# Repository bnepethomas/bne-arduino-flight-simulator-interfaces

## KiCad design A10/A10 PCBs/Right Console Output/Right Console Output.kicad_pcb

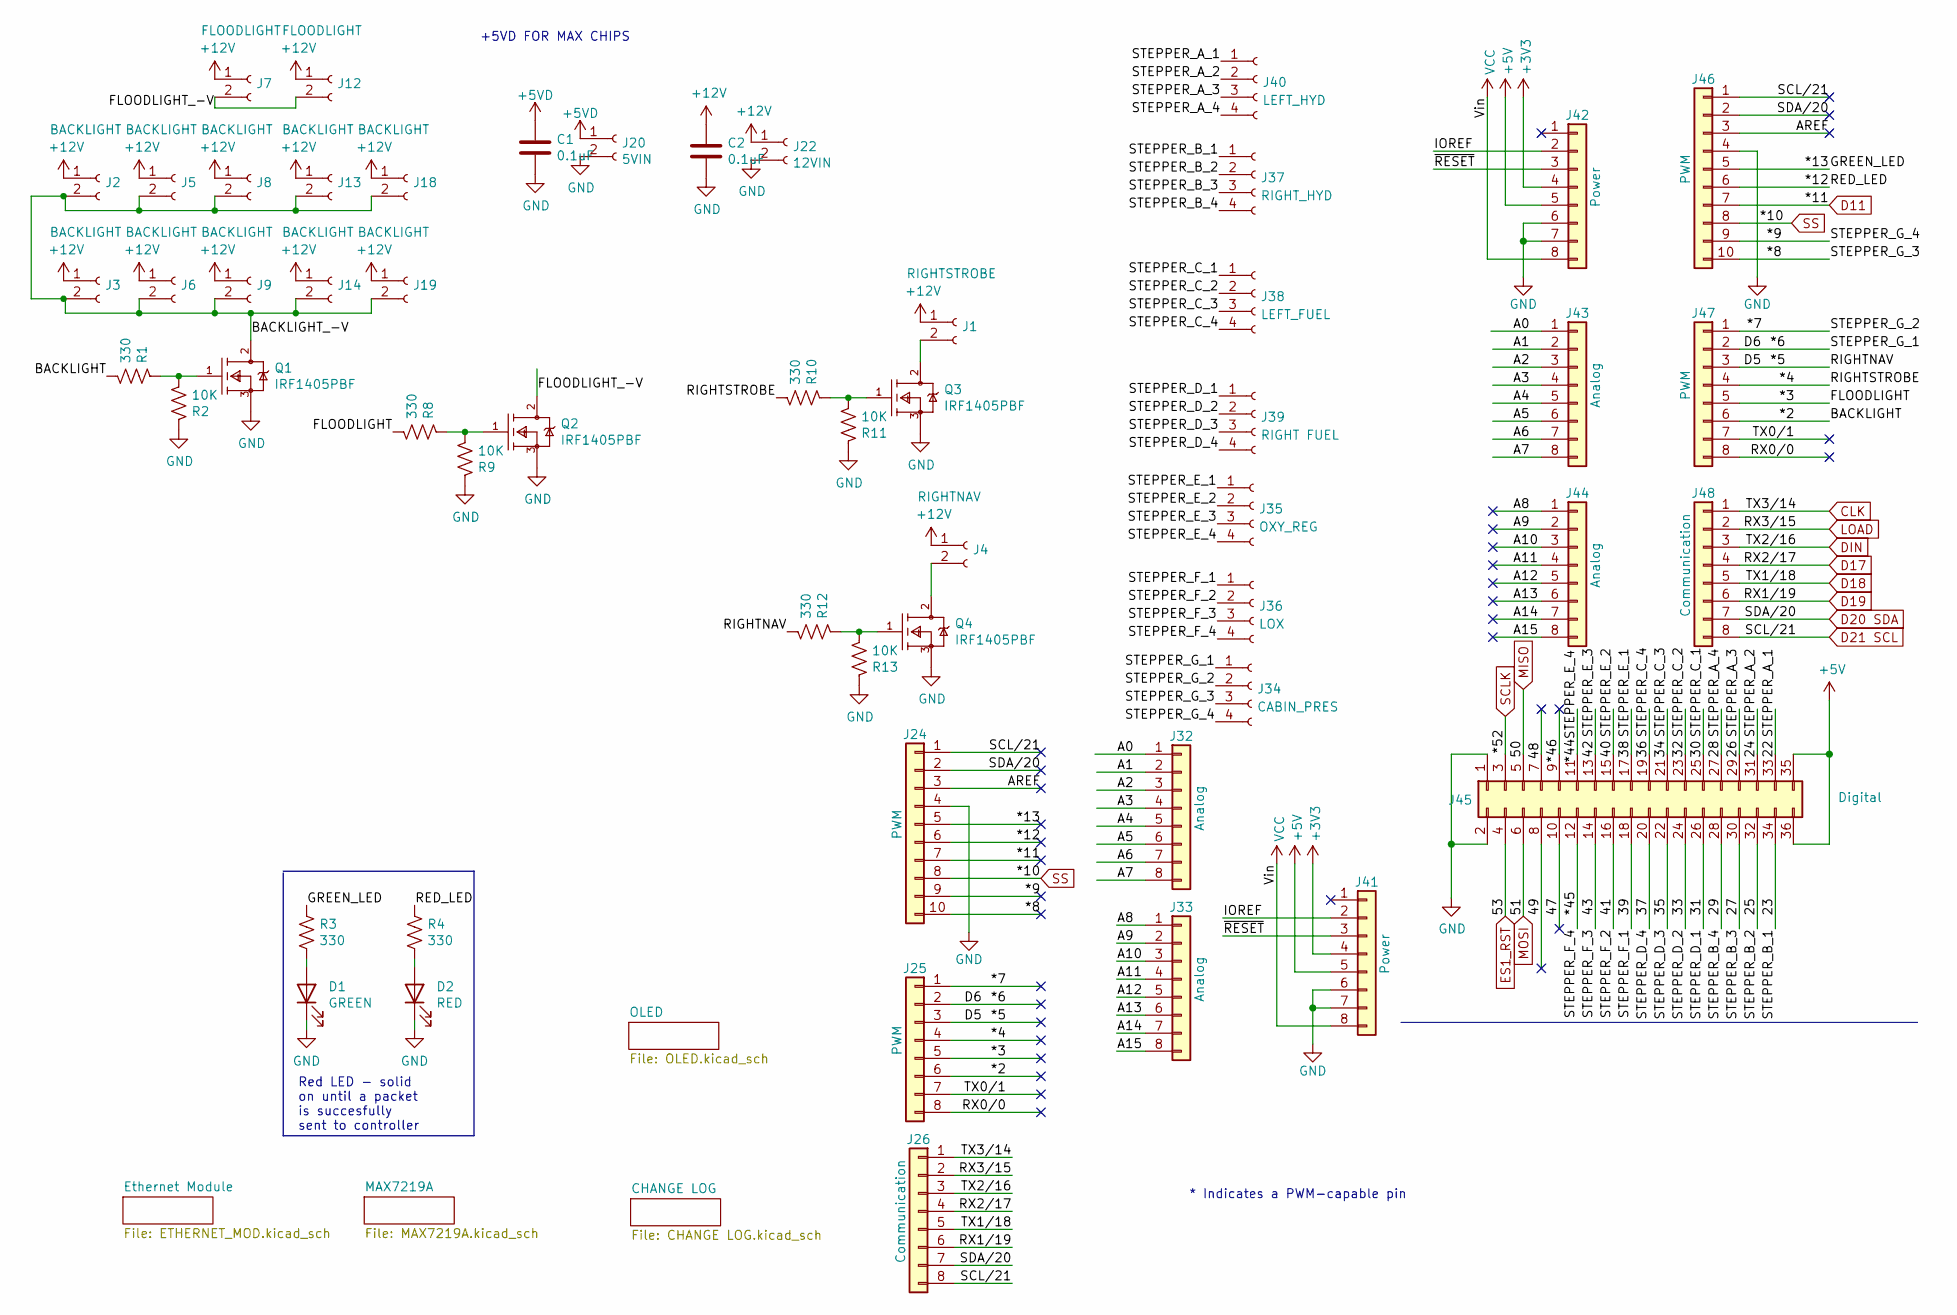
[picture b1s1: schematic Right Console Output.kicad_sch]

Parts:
C1, C2: 0.1uF; C_Disc_D4.3mm_W1.9mm_P5.00mm
D1: GREEN; LED_D3.0mm
D2: RED; LED_D3.0mm
J1: RIGHTSTROBE; Molex_KK-254_AE-6410-02A_1x02_P2.54mm_Vertical
J2, J3, J5, J6, J8, J9, J13, J14, J18, J19: BACKLIGHT; Molex_KK-254_AE-6410-02A_1x02_P2.54mm_Vertical
J4: RIGHTNAV; Molex_KK-254_AE-6410-02A_1x02_P2.54mm_Vertical
J7, J12: FLOODLIGHT; Molex_KK-254_AE-6410-02A_1x02_P2.54mm_Vertical
J20: 5VIN; BarrelJack_Horizontal
J22: 12VIN; BarrelJack_Horizontal
J24, J46: PWM; PinSocket_1x10_P2.54mm_Vertical
J25, J47: PWM; PinSocket_1x08_P2.54mm_Vertical
J26, J48: Communication; PinSocket_1x08_P2.54mm_Vertical
J32, J33, J43, J44: Analog; PinSocket_1x08_P2.54mm_Vertical
J34: CABIN_PRES; Molex_KK-254_AE-6410-04A_1x04_P2.54mm_Vertical
J35: OXY_REG; Molex_KK-254_AE-6410-04A_1x04_P2.54mm_Vertical
J36: LOX; Molex_KK-254_AE-6410-04A_1x04_P2.54mm_Vertical
J37: RIGHT_HYD; Molex_KK-254_AE-6410-04A_1x04_P2.54mm_Vertical
J38: LEFT_FUEL; Molex_KK-254_AE-6410-04A_1x04_P2.54mm_Vertical
J39: RIGHT FUEL; Molex_KK-254_AE-6410-04A_1x04_P2.54mm_Vertical
J40: LEFT_HYD; Molex_KK-254_AE-6410-04A_1x04_P2.54mm_Vertical
J41, J42: Power; PinSocket_1x08_P2.54mm_Vertical
J45: Digital; PinSocket_2x18_P2.54mm_Vertical
Q1, Q2, Q3, Q4: IRF1405PBF; TO-220-3_Vertical; mouser part number 942-IRF1405PBF; digikey description MOSFET N-CH 55V 169A TO-220AB
R1, R3, R4, R8, R10, R12: 330; R_Axial_DIN0204_L3.6mm_D1.6mm_P2.54mm_Vertical
R2, R9, R11, R13: 10K; R_Axial_DIN0204_L3.6mm_D1.6mm_P2.54mm_Vertical

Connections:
+3V3: J41.4, J42.4; also elsewhere on the board
+5V: J41.5, J42.5, J45.35, J45.36
+5VD: C1.1, J20.1; also elsewhere on the board
+12V: C2.1, J1.1, J2.1, J3.1, J4.1, J5.1, J6.1, J7.1, J8.1, J9.1, J12.1, J13.1, J14.1, J18.1, J19.1, J22.1
/22: J40.1, J45.33
/23: J37.1, J45.34
/24: J40.2, J45.31
/25: J37.2, J45.32
/26: J40.3, J45.29
/27: J37.3, J45.30
/28: J40.4, J45.27
/29: J37.4, J45.28
/30: J38.1, J45.25
/31: J39.1, J45.26
/32: J38.2, J45.23
/33: J39.2, J45.24
/34: J38.3, J45.21
/35: J39.3, J45.22
/36: J38.4, J45.19
/37: J39.4, J45.20
/38: J35.1, J45.17
/39: J36.1, J45.18
/40: J35.2, J45.15
/41: J36.2, J45.16
/42: J35.3, J45.13
/43: J36.3, J45.14
/47: J45.10
/48: J45.7
/49: J45.8
/*2: J25.6, J47.6, R1.2
/*3: J25.5, J47.5, R8.2
/*4: J25.4, J47.4, R10.2
/*5: J25.3, J47.3, R12.2
/*6: J25.2, J34.1, J47.2
/*7: J25.1, J34.2, J47.1
/*8: J24.10, J34.3, J46.10
/*9: J24.9, J34.4, J46.9
/*12: J24.6, J46.6, R4.1
/*13: J24.5, J46.5, R3.1
/*44: J35.4, J45.11
/*45: J36.4, J45.12
/*46: J45.9
/A0: J32.1, J43.1
/A1: J32.2, J43.2
/A2: J32.3, J43.3
/A3: J32.4, J43.4
/A4: J32.5, J43.5
/A5: J32.6, J43.6
/A6: J32.7, J43.7
/A7: J32.8, J43.8
/A8: J33.1, J44.1
/A9: J33.2, J44.2
/A10: J33.3, J44.3
/A11: J33.4, J44.4
/A12: J33.5, J44.5
/A13: J33.6, J44.6
/A14: J33.7, J44.7
/A15: J33.8, J44.8
/AREF: J24.3, J46.3
/BACKLIGHT_-V: J2.2, J3.2, J5.2, J6.2, J8.2, J9.2, J13.2, J14.2, J18.2, J19.2, Q1.2 (D)
/FLOODLIGHT_-V: J7.2, J12.2, Q2.2 (D)
/IOREF: J41.2, J42.2
/RX0/0: J25.8, J47.8
/TX0/1: J25.7, J47.7
/~RESET: J41.3, J42.3
CLK: J26.1, J48.1; also elsewhere on the board
D11: J24.7, J46.7
D17: J26.4, J48.4; also elsewhere on the board
D18: J26.5, J48.5; also elsewhere on the board
D19: J26.6, J48.6; also elsewhere on the board
D20 SDA: J24.2, J26.7, J46.2, J48.7; also elsewhere on the board
D21 SCL: J24.1, J26.8, J46.1, J48.8; also elsewhere on the board
DIN: J26.3, J48.3; also elsewhere on the board
ES1_RST: J45.4; also elsewhere on the board
GND: C1.2, C2.2, D1.1 (K), D2.1 (K), J20.2, J22.2, J24.4, J41.6, J41.7, J42.6, J42.7, J45.1, J45.2, J46.4, Q1.3 (S), Q2.3 (S), Q3.3 (S), Q4.3 (S), R2.1, R9.1, R11.1, R13.1; also elsewhere on the board
LOAD: J26.2, J48.2; also elsewhere on the board
MISO: J45.5; also elsewhere on the board
MOSI: J45.6; also elsewhere on the board
unnamed: D1.2 (A), R3.2
unnamed: D2.2 (A), R4.2
unnamed: J1.2, Q3.2 (D)
unnamed: J4.2, Q4.2 (D)
unnamed: Q1.1 (G), R1.1, R2.2
unnamed: Q2.1 (G), R8.1, R9.2
unnamed: Q3.1 (G), R10.1, R11.2
unnamed: Q4.1 (G), R12.1, R13.2
SCLK: J45.3; also elsewhere on the board
SS: J24.8, J46.8; also elsewhere on the board
VCC: J41.8, J42.8

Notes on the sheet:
Red LED - solid on until a packet is succesfully sent to controller
+5VD FOR MAX CHIPS
* Indicates a PWM-capable pin

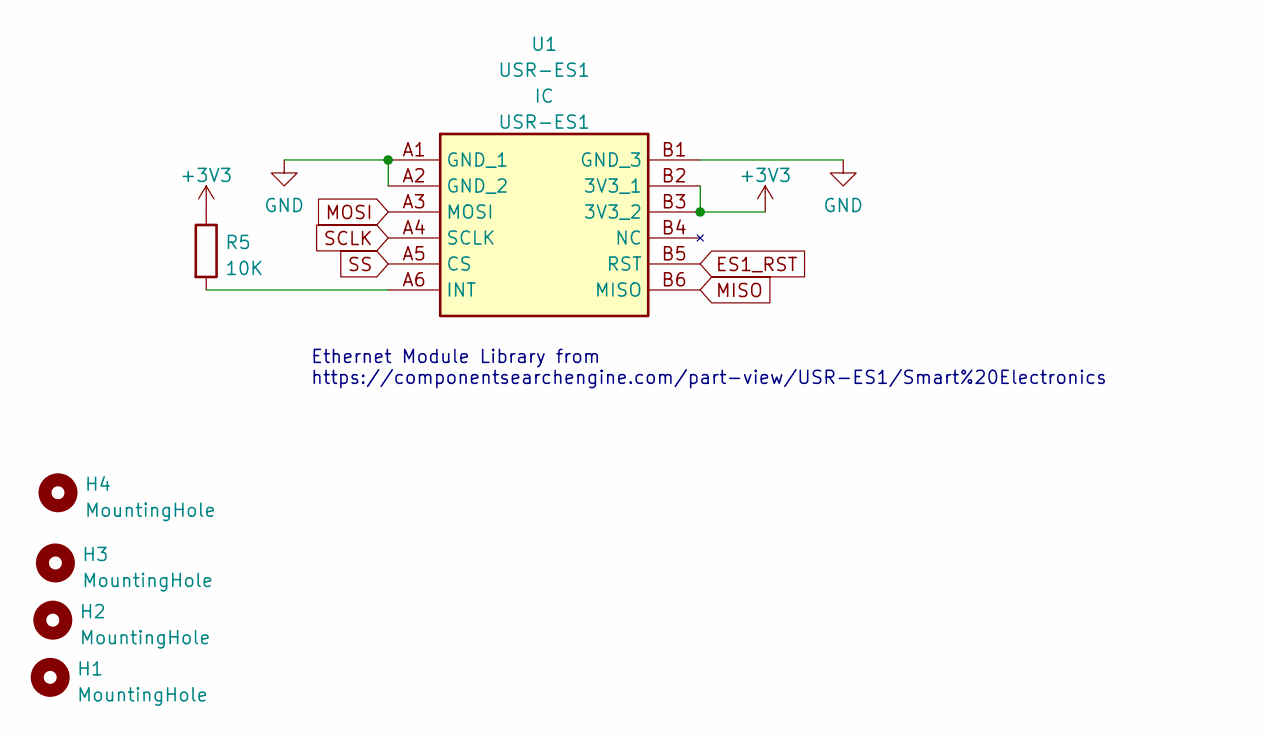
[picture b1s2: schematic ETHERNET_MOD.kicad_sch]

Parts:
H1, H2, H3, H4: MountingHole; MountingHole_3.2mm
R5: 10K; R_Axial_DIN0204_L3.6mm_D1.6mm_P2.54mm_Vertical
U1: USR-ES1; USRES1; Manufacturer_Part_Number USR-ES1

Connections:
+3V3: R5.1, U1.B2 (3V3_1), U1.B3 (3V3_2); also elsewhere on the board
ES1_RST: U1.B5 (RST); also elsewhere on the board
GND: U1.A1 (GND_1), U1.A2 (GND_2), U1.B1 (GND_3); also elsewhere on the board
MISO: U1.B6 (MISO); also elsewhere on the board
MOSI: U1.A3 (MOSI); also elsewhere on the board
unnamed: R5.2, U1.A6 (INT)
SCLK: U1.A4 (SCLK); also elsewhere on the board
SS: U1.A5 (CS); also elsewhere on the board

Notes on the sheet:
Ethernet Module Library from https://componentsearchengine.com/part-view/USR-ES1/Smart%20Electronics

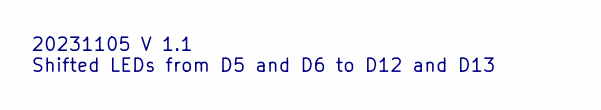
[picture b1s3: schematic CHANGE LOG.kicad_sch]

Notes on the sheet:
20231105 V 1.1 Shifted LEDs from D5 and D6 to D12 and D13

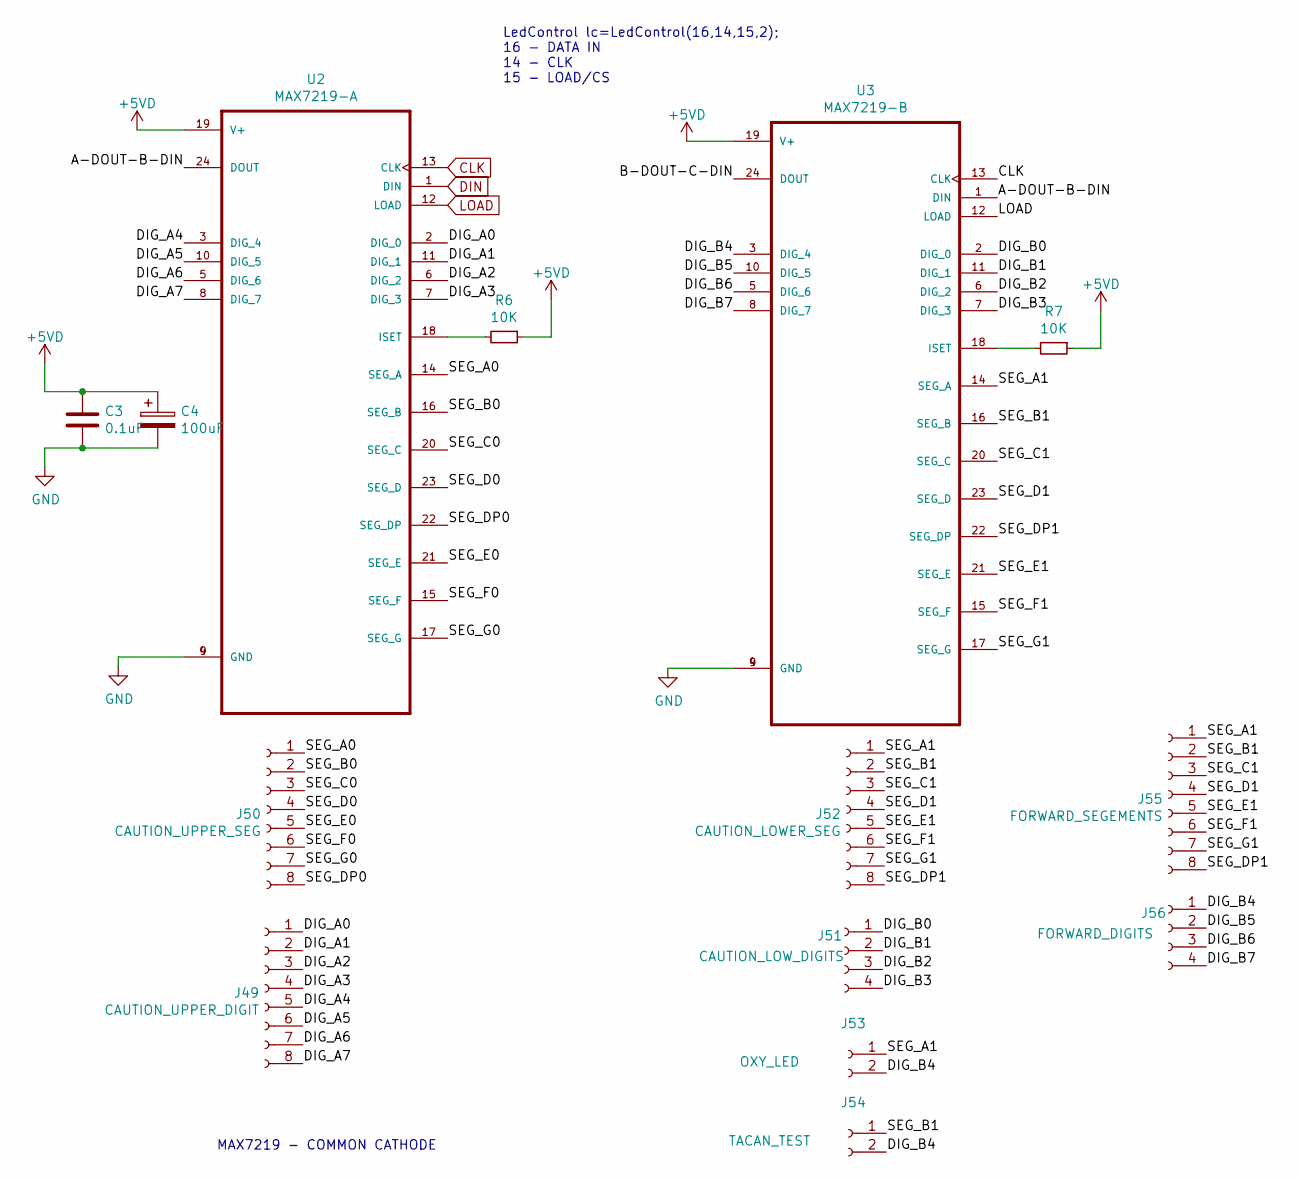
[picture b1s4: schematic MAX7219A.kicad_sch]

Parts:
C3: 0.1uF; C_Disc_D5.1mm_W3.2mm_P5.00mm
C4: 100uF; CP_Radial_D8.0mm_P5.00mm
J49: CAUTION_UPPER_DIGIT; Molex_KK-254_AE-6410-08A_1x08_P2.54mm_Vertical
J50: CAUTION_UPPER_SEG; Molex_KK-254_AE-6410-08A_1x08_P2.54mm_Vertical
J51: CAUTION_LOW_DIGITS; Molex_KK-254_AE-6410-04A_1x04_P2.54mm_Vertical
J52: CAUTION_LOWER_SEG; Molex_KK-254_AE-6410-08A_1x08_P2.54mm_Vertical
J53: OXY_LED; Molex_KK-254_AE-6410-02A_1x02_P2.54mm_Vertical
J54: TACAN_TEST; Molex_KK-254_AE-6410-02A_1x02_P2.54mm_Vertical
J55: FORWARD_SEGEMENTS; Molex_KK-254_AE-6410-08A_1x08_P2.54mm_Vertical
J56: FORWARD_DIGITS; Molex_KK-254_AE-6410-04A_1x04_P2.54mm_Vertical
R6, R7: 10K; R_Axial_DIN0204_L3.6mm_D1.6mm_P2.54mm_Vertical
U2: MAX7219-A; DIP-24_W7.62mm_Socket
U3: MAX7219-B; DIP-24_W7.62mm_Socket

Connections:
+5VD: C3.1, C4.1, R6.1, R7.1, U2.19 (V+), U3.19 (V+); also elsewhere on the board
/MAX7219A/A-DOUT-B-DIN: U2.24 (DOUT), U3.1 (DIN)
/MAX7219A/B-DOUT-C-DIN: U3.24 (DOUT)
/MAX7219A/DIG_A0: J49.1, U2.2 (DIG_0)
/MAX7219A/DIG_A1: J49.2, U2.11 (DIG_1)
/MAX7219A/DIG_A2: J49.3, U2.6 (DIG_2)
/MAX7219A/DIG_A3: J49.4, U2.7 (DIG_3)
/MAX7219A/DIG_A4: J49.5, U2.3 (DIG_4)
/MAX7219A/DIG_A5: J49.6, U2.10 (DIG_5)
/MAX7219A/DIG_A6: J49.7, U2.5 (DIG_6)
/MAX7219A/DIG_A7: J49.8, U2.8 (DIG_7)
/MAX7219A/DIG_B0: J51.1, U3.2 (DIG_0)
/MAX7219A/DIG_B1: J51.2, U3.11 (DIG_1)
/MAX7219A/DIG_B2: J51.3, U3.6 (DIG_2)
/MAX7219A/DIG_B3: J51.4, U3.7 (DIG_3)
/MAX7219A/DIG_B4: J53.2, J54.2, J56.1, U3.3 (DIG_4)
/MAX7219A/DIG_B5: J56.2, U3.10 (DIG_5)
/MAX7219A/DIG_B6: J56.3, U3.5 (DIG_6)
/MAX7219A/DIG_B7: J56.4, U3.8 (DIG_7)
/MAX7219A/SEG_A0: J50.1, U2.14 (SEG_A)
/MAX7219A/SEG_A1: J52.1, J53.1, J55.1, U3.14 (SEG_A)
/MAX7219A/SEG_B0: J50.2, U2.16 (SEG_B)
/MAX7219A/SEG_B1: J52.2, J54.1, J55.2, U3.16 (SEG_B)
/MAX7219A/SEG_C0: J50.3, U2.20 (SEG_C)
/MAX7219A/SEG_C1: J52.3, J55.3, U3.20 (SEG_C)
/MAX7219A/SEG_D0: J50.4, U2.23 (SEG_D)
/MAX7219A/SEG_D1: J52.4, J55.4, U3.23 (SEG_D)
/MAX7219A/SEG_DP0: J50.8, U2.22 (SEG_DP)
/MAX7219A/SEG_DP1: J52.8, J55.8, U3.22 (SEG_DP)
/MAX7219A/SEG_E0: J50.5, U2.21 (SEG_E)
/MAX7219A/SEG_E1: J52.5, J55.5, U3.21 (SEG_E)
/MAX7219A/SEG_F0: J50.6, U2.15 (SEG_F)
/MAX7219A/SEG_F1: J52.6, J55.6, U3.15 (SEG_F)
/MAX7219A/SEG_G0: J50.7, U2.17 (SEG_G)
/MAX7219A/SEG_G1: J52.7, J55.7, U3.17 (SEG_G)
CLK: U2.13 (CLK), U3.13 (CLK); also elsewhere on the board
DIN: U2.1 (DIN); also elsewhere on the board
GND: C3.2, C4.2, U2.4 (GND), U2.9 (GND), U3.4 (GND), U3.9 (GND); also elsewhere on the board
LOAD: U2.12 (LOAD), U3.12 (LOAD); also elsewhere on the board
unnamed: R6.2, U2.18 (ISET)
unnamed: R7.2, U3.18 (ISET)

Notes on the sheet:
LedControl lc=LedControl(16,14,15,2); 16 - DATA IN 14 - CLK 15 - LOAD/CS
MAX7219 - COMMON CATHODE

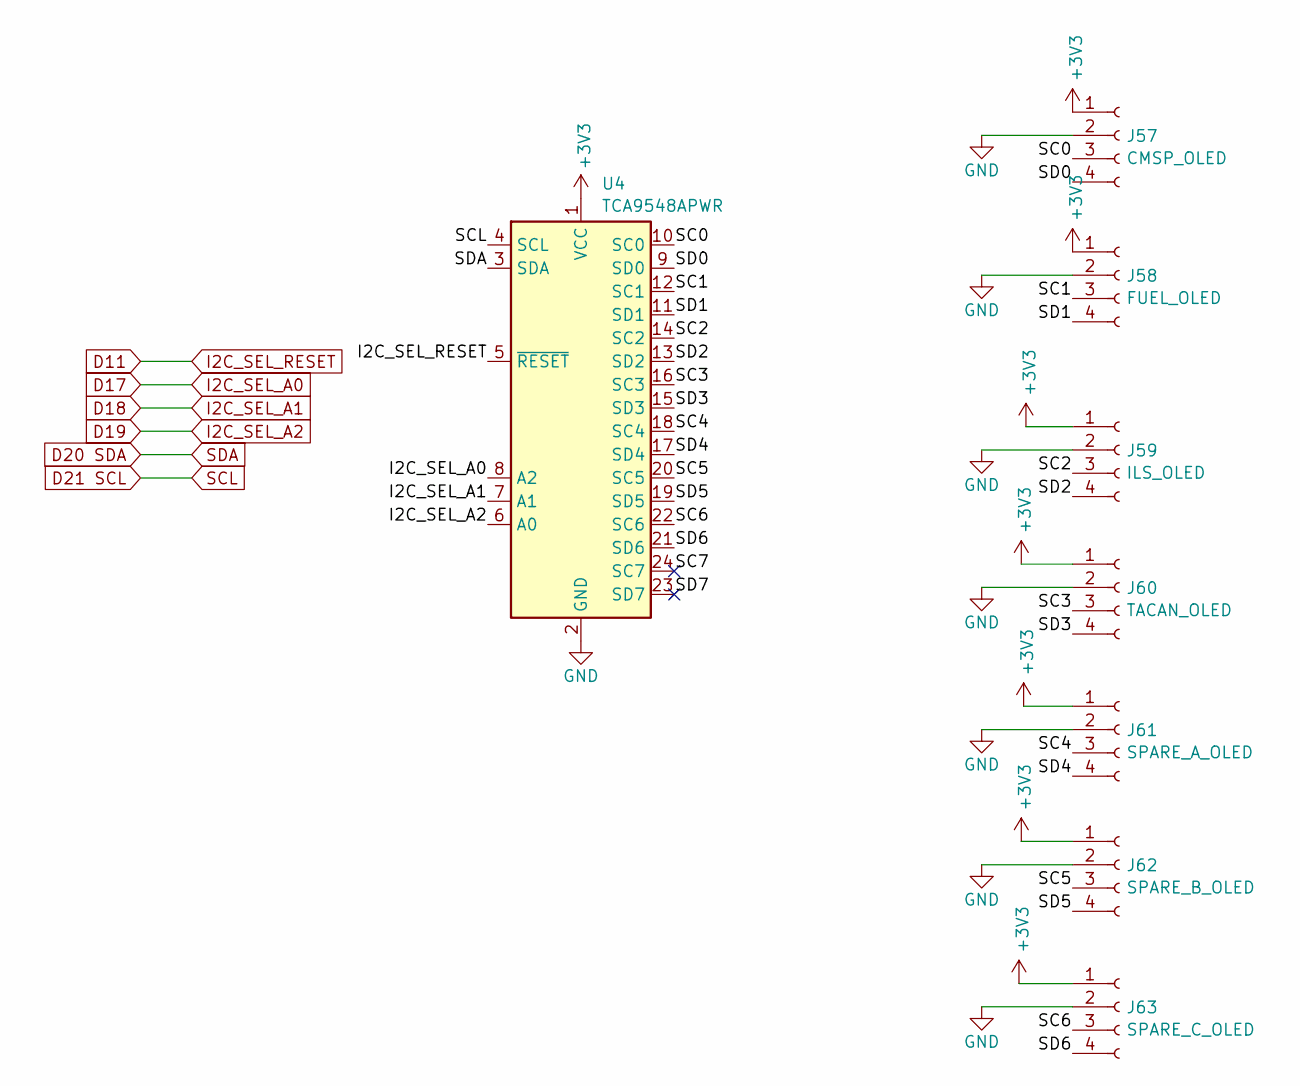
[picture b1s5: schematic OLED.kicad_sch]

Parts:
J57: CMSP_OLED; Molex_KK-254_AE-6410-04A_1x04_P2.54mm_Vertical
J58: FUEL_OLED; Molex_KK-254_AE-6410-04A_1x04_P2.54mm_Vertical
J59: ILS_OLED; Molex_KK-254_AE-6410-04A_1x04_P2.54mm_Vertical
J60: TACAN_OLED; Molex_KK-254_AE-6410-04A_1x04_P2.54mm_Vertical
J61: SPARE_A_OLED; Molex_KK-254_AE-6410-04A_1x04_P2.54mm_Vertical
J62: SPARE_B_OLED; Molex_KK-254_AE-6410-04A_1x04_P2.54mm_Vertical
J63: SPARE_C_OLED; Molex_KK-254_AE-6410-04A_1x04_P2.54mm_Vertical
U4: TCA9548APWR; DIP-24_TCA9548A

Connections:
+3V3: J57.1, J58.1, J59.1, J60.1, J61.1, J62.1, J63.1, U4.1 (VCC); also elsewhere on the board
/OLED/SC0: J57.3, U4.10 (SC0)
/OLED/SC1: J58.3, U4.12 (SC1)
/OLED/SC2: J59.3, U4.14 (SC2)
/OLED/SC3: J60.3, U4.16 (SC3)
/OLED/SC4: J61.3, U4.18 (SC4)
/OLED/SC5: J62.3, U4.20 (SC5)
/OLED/SC6: J63.3, U4.22 (SC6)
/OLED/SC7: U4.24 (SC7)
/OLED/SD0: J57.4, U4.9 (SD0)
/OLED/SD1: J58.4, U4.11 (SD1)
/OLED/SD2: J59.4, U4.13 (SD2)
/OLED/SD3: J60.4, U4.15 (SD3)
/OLED/SD4: J61.4, U4.17 (SD4)
/OLED/SD5: J62.4, U4.19 (SD5)
/OLED/SD6: J63.4, U4.21 (SD6)
/OLED/SD7: U4.23 (SD7)
D16: U4.5 (~RESET)
D17: U4.8 (A2); also elsewhere on the board
D18: U4.7 (A1); also elsewhere on the board
D19: U4.6 (A0); also elsewhere on the board
D20 SDA: U4.3 (SDA); also elsewhere on the board
D21 SCL: U4.4 (SCL); also elsewhere on the board
GND: J57.2, J58.2, J59.2, J60.2, J61.2, J62.2, J63.2, U4.2 (GND); also elsewhere on the board

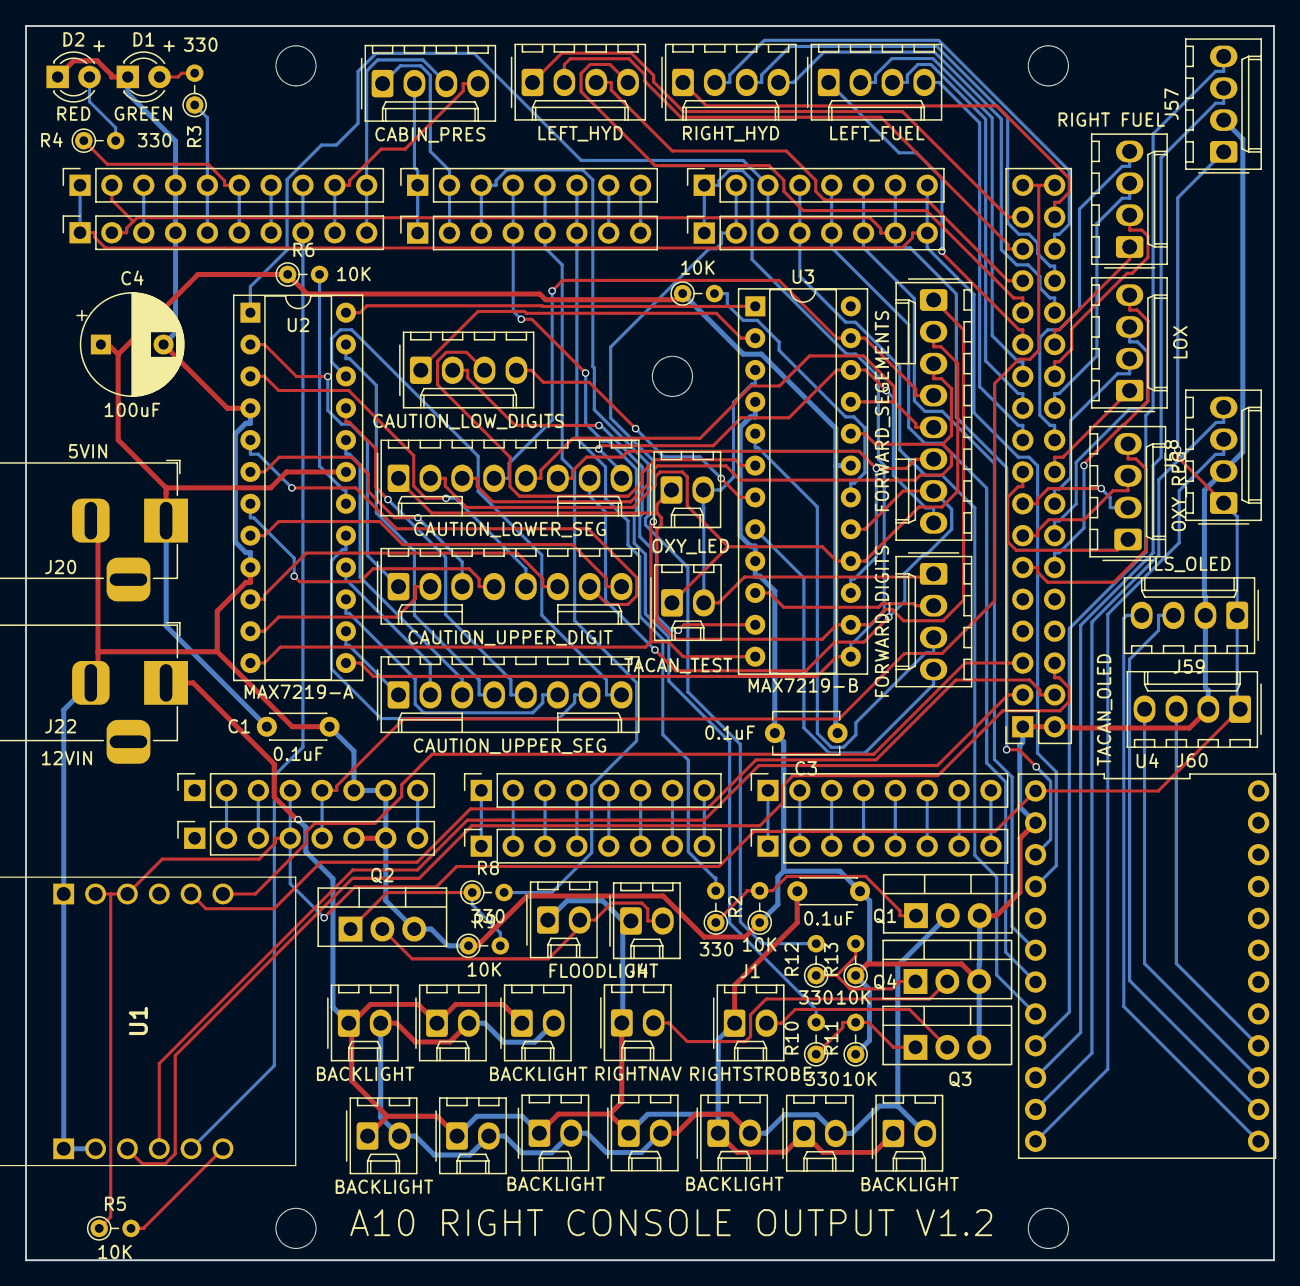
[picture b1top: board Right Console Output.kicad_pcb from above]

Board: 2 copper layers, 99.5 x 98.4 mm, 80 parts (0 on the bottom side), 129 nets.

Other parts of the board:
MH1: MountingHole_3.2mm

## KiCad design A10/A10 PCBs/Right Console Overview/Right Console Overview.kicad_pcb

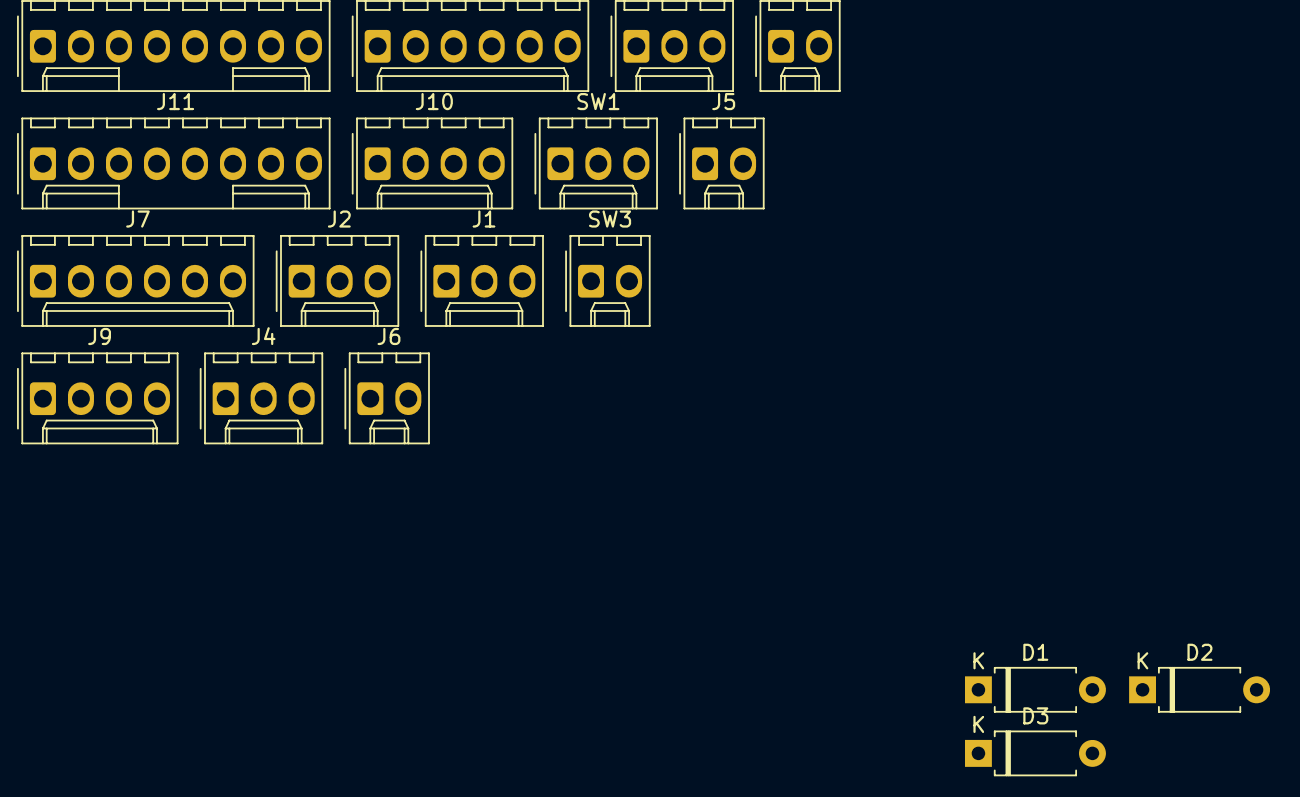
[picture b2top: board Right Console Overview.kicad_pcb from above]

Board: 2 copper layers, 18 parts (0 on the bottom side), 10 nets, no tracks yet.

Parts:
D1, D2, D3: D; D_A-405_P7.62mm_Horizontal
J1, J2, J3, J4: Conn_01x03_Female; Molex_KK-254_AE-6410-03A_1x03_P2.54mm_Vertical
J5, J6: Conn_01x02_Female; Molex_KK-254_AE-6410-02A_1x02_P2.54mm_Vertical
J7: TACAN ROTARY SWITCH; Molex_KK-254_AE-6410-06A_1x06_P2.54mm_Vertical
J8: Conn_01x08_Female; Molex_KK-254_AE-6410-08A_1x08_P2.54mm_Vertical
J9: I2C In; Molex_KK-254_AE-6410-04A_1x04_P2.54mm_Vertical
J10: I2C Out; Molex_KK-254_AE-6410-04A_1x04_P2.54mm_Vertical
J11: INPUT COLS; Molex_KK-254_AE-6410-08A_1x08_P2.54mm_Vertical
SW1: Right Encoder; Molex_KK-254_AE-6410-03A_1x03_P2.54mm_Vertical
SW2: SW_Rotary2x6; Molex_KK-254_AE-6410-06A_1x06_P2.54mm_Vertical
SW3: Test; Molex_KK-254_AE-6410-02A_1x02_P2.54mm_Vertical
SW4: Encoder_Push; Molex_KK-254_AE-6410-02A_1x02_P2.54mm_Vertical

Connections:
/TACAN/COL1: D3.2 (A), J11.1
/TACAN/COL2: D1.2 (A), J11.2
/TACAN/ROW1: J7.2, SW3.2, SW4.2
unnamed: D1.1 (K), SW3.1
unnamed: D2.1 (K), SW4.1
unnamed: D3.1 (K), J7.1
unnamed: J9.1, J10.1
unnamed: J9.2, J10.2
unnamed: J9.3, J10.3
unnamed: J9.4, J10.4

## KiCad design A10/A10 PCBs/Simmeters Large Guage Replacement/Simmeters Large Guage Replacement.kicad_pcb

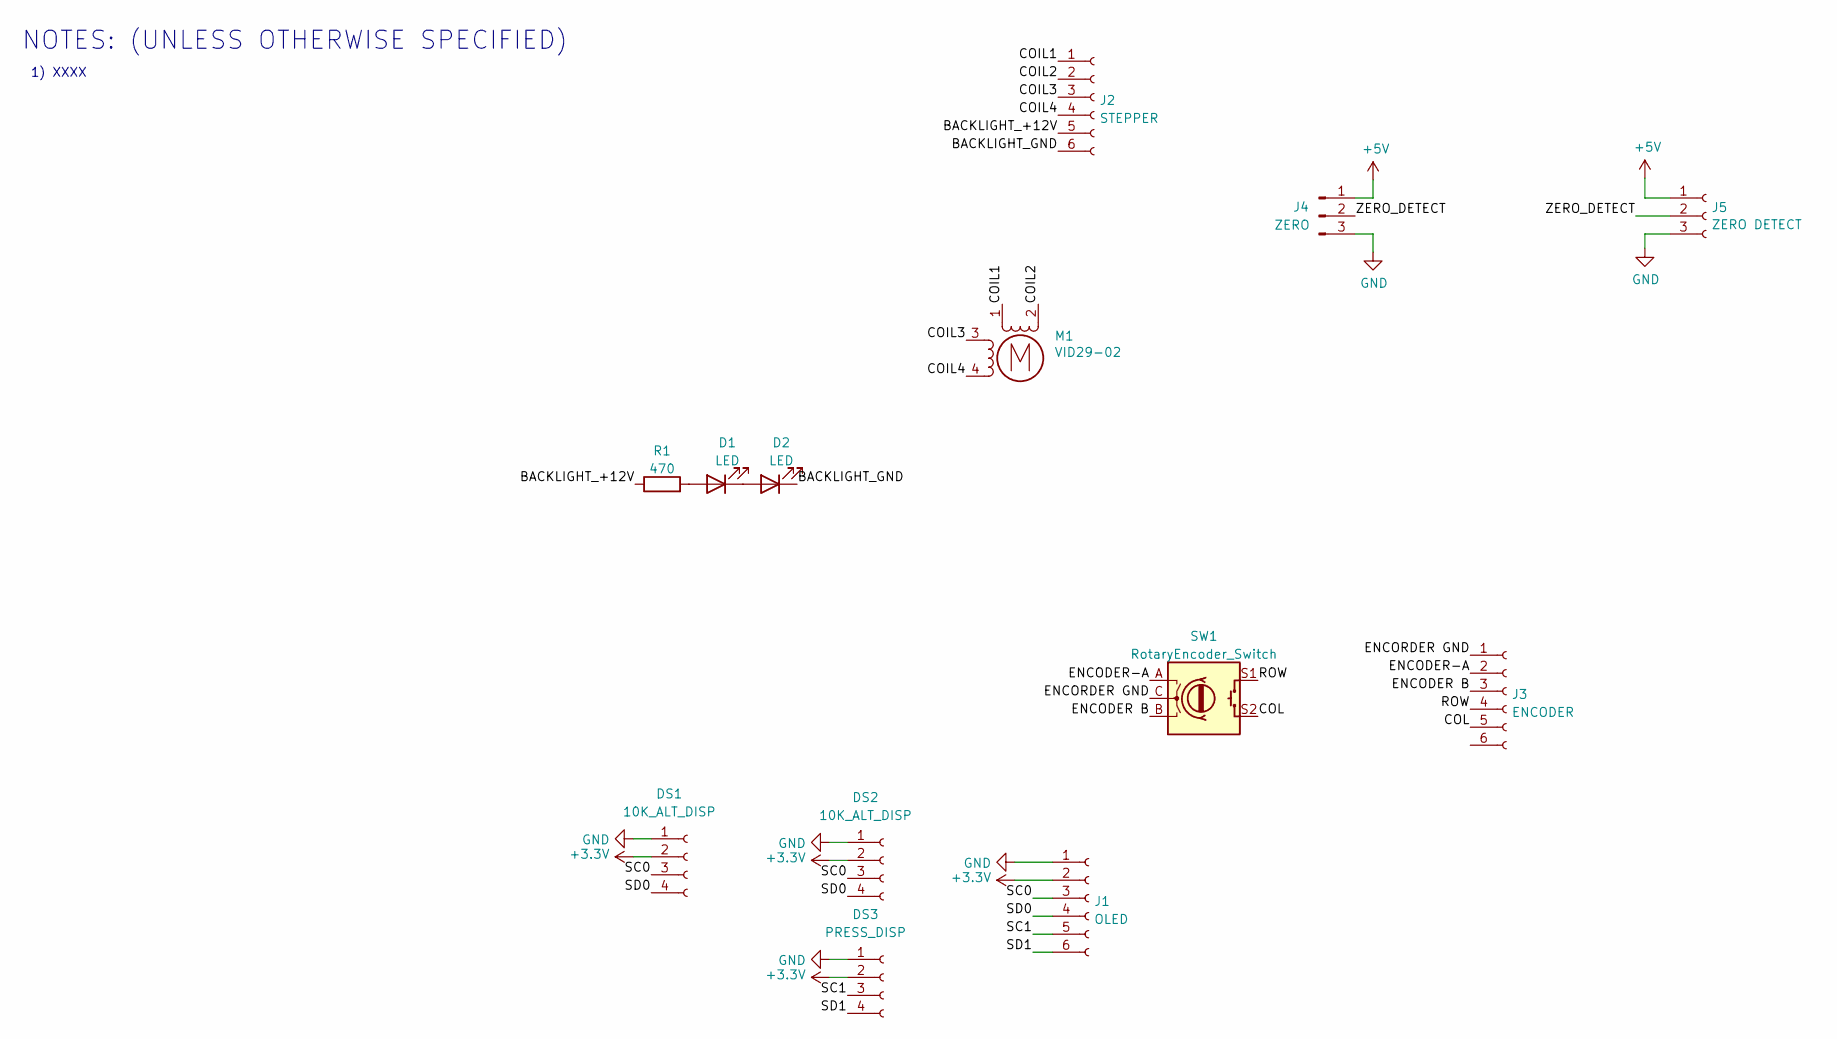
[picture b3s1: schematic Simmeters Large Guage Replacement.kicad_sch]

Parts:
D1, D2: LED; LED_D3.0mm
DS1, DS2: 10K_ALT_DISP; PinSocket_1x04_P2.54mm_Vertical
DS3: PRESS_DISP; PinSocket_1x04_P2.54mm_Vertical
J1: OLED; Molex_KK-254_AE-6410-06A_1x06_P2.54mm_Vertical
J2: STEPPER; Molex_KK-254_AE-6410-06A_1x06_P2.54mm_Vertical
J3: ENCODER; Molex_KK-254_AE-6410-06A_1x06_P2.54mm_Vertical
J4: ZERO; PinHeader_1x03_P2.54mm_Vertical
J5: ZERO DETECT; Molex_KK-254_AE-6410-03A_1x03_P2.54mm_Vertical
M1: VID29-02
R1: 470; R_Axial_DIN0204_L3.6mm_D1.6mm_P1.90mm_Vertical
SW1: RotaryEncoder_Switch; RotaryEncoder_Alps_EC11E-Switch_Vertical_H20mm

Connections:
+3V3: DS1.2, DS2.2, DS3.2, J1.2
+5V: J4.1, J5.1
/BACKLIGHT_+12V: J2.5, R1.1
/BACKLIGHT_GND: D2.1 (K), J2.6
/COIL1: J2.1, M1.1
/COIL2: J2.2, M1.2 (-)
/COIL3: J2.3, M1.3
/COIL4: J2.4, M1.4
/COL: J3.5, SW1.S2
/ENCODER B: J3.3, SW1.B
/ENCODER-A: J3.2, SW1.A
/ENCORDER GND: J3.1, SW1.C
/ROW: J3.4, SW1.S1
/SC0: DS1.3, DS2.3, J1.3
/SC1: DS3.3, J1.5
/SD0: DS1.4, DS2.4, J1.4
/SD1: DS3.4, J1.6
/ZERO_DETECT: J4.2, J5.2
GND: DS1.1, DS2.1, DS3.1, J1.1, J4.3, J5.3
unnamed: D1.2 (A), R1.2
unnamed: D1.1 (K), D2.2 (A)

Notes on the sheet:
1) XXXX
NOTES: (UNLESS OTHERWISE SPECIFIED)

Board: 2 copper layers, 13 parts (5 on the bottom side), 21 nets, no tracks yet.

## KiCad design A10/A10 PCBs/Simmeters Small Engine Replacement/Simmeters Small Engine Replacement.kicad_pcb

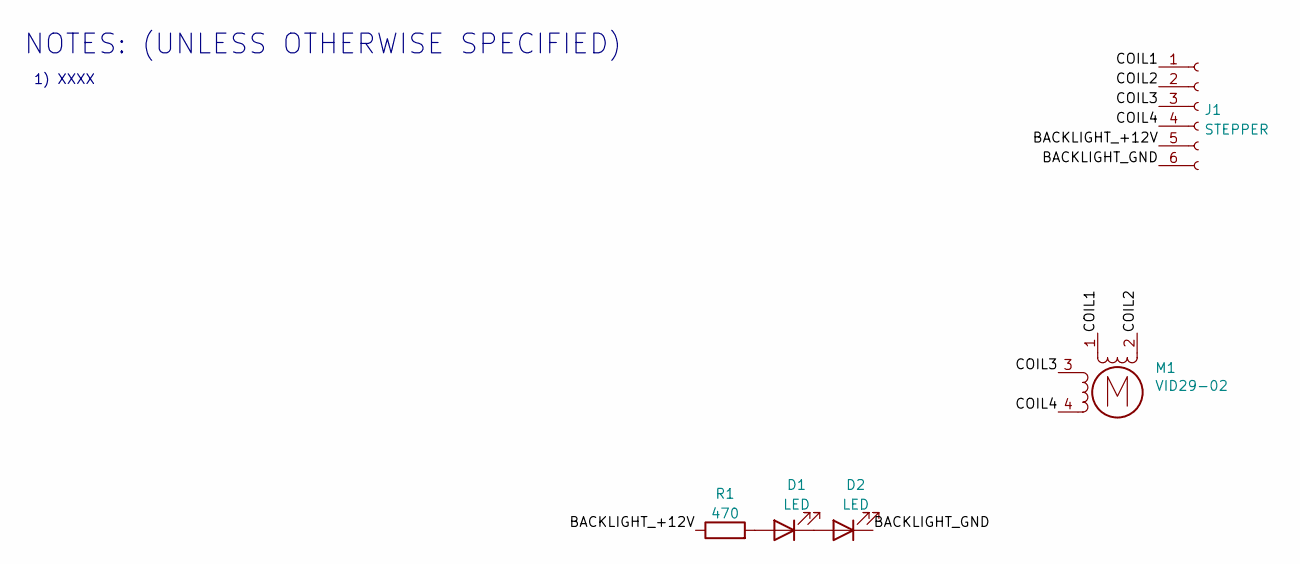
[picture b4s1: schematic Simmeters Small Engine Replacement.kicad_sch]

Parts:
D1, D2: LED; LED_D3.0mm
J1: STEPPER; Molex_KK-254_AE-6410-06A_1x06_P2.54mm_Vertical
M1: VID29-02; VID29-05P
R1: 470; R_Axial_DIN0204_L3.6mm_D1.6mm_P1.90mm_Vertical

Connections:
/BACKLIGHT_+12V: J1.5, R1.1
/BACKLIGHT_GND: D2.1 (K), J1.6
/COIL1: J1.1, M1.1
/COIL2: J1.2, M1.2 (-)
/COIL3: J1.3, M1.3
/COIL4: J1.4, M1.4
unnamed: D1.1 (K), D2.2 (A)
unnamed: D1.2 (A), R1.2

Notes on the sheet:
1) XXXX
NOTES: (UNLESS OTHERWISE SPECIFIED)

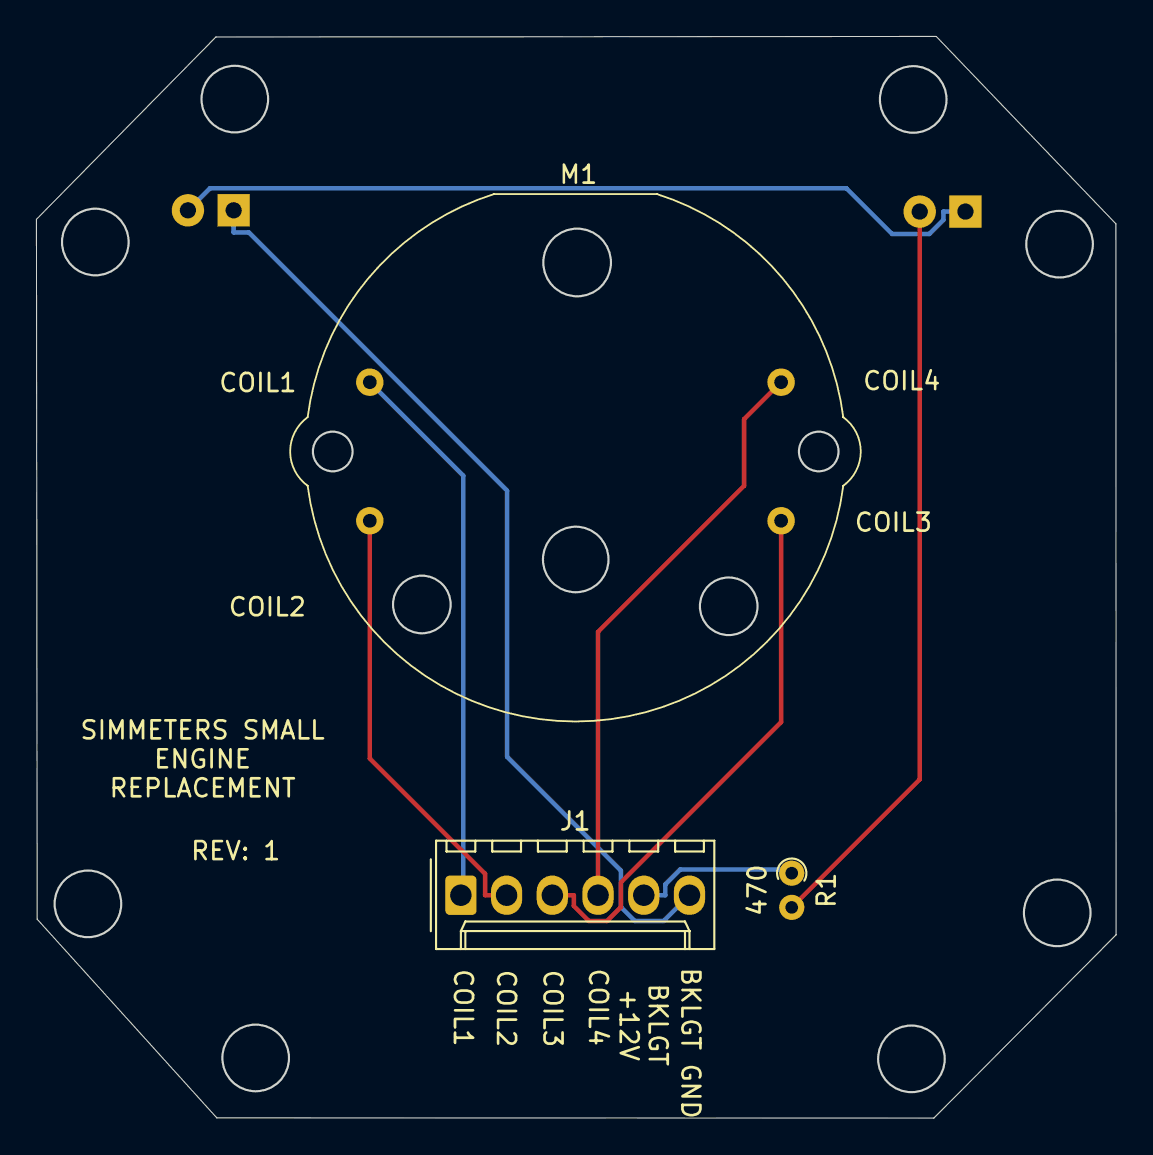
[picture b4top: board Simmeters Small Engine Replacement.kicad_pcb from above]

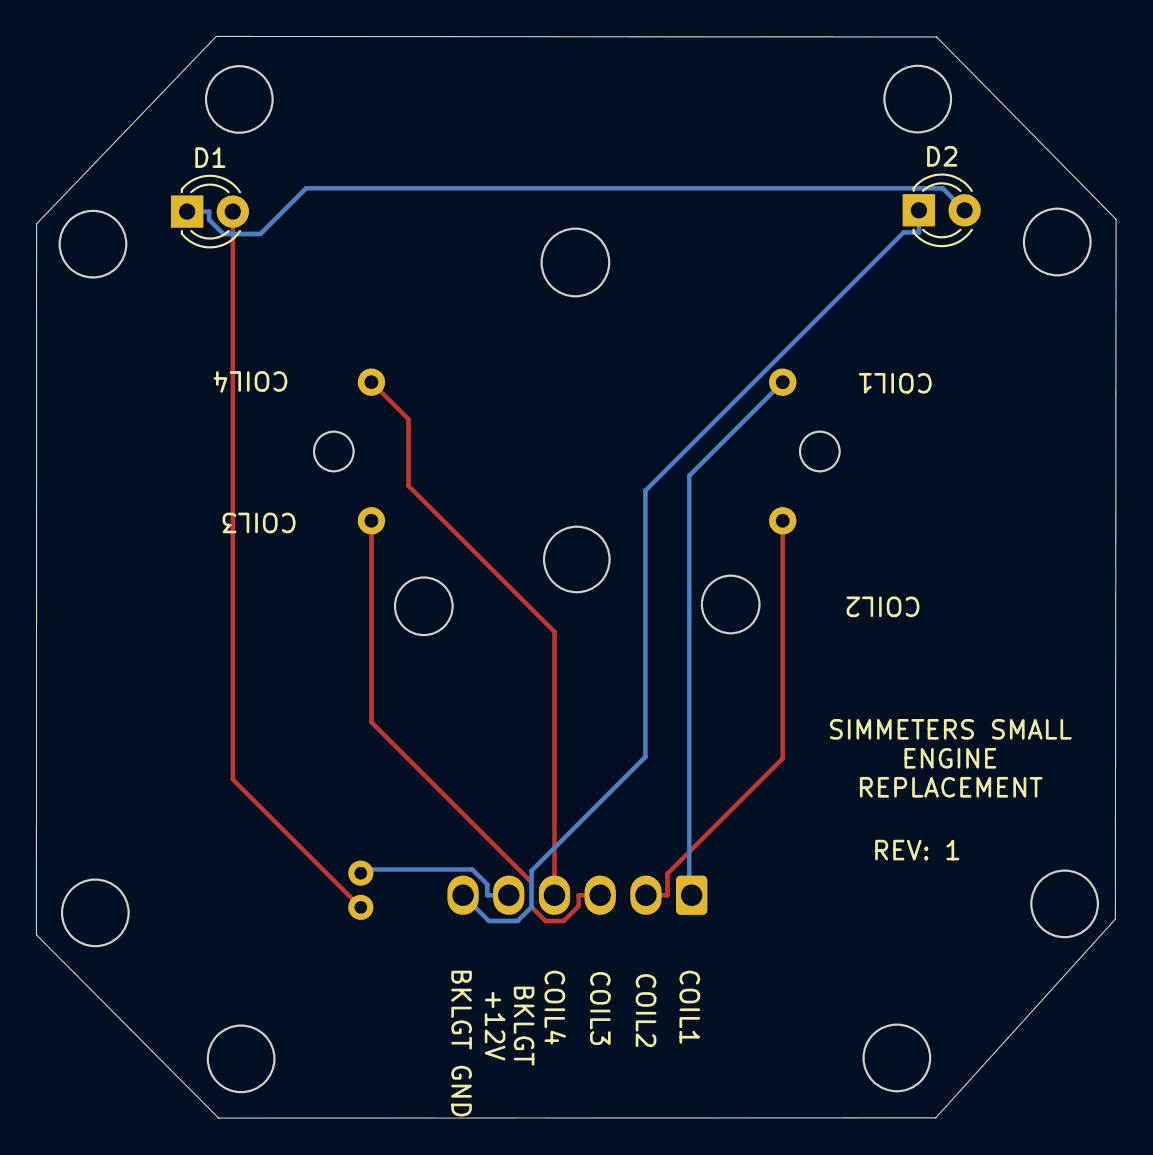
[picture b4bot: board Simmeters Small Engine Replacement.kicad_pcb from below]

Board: 2 copper layers, 60.0 x 60.1 mm, 5 parts (2 on the bottom side), 8 nets.
